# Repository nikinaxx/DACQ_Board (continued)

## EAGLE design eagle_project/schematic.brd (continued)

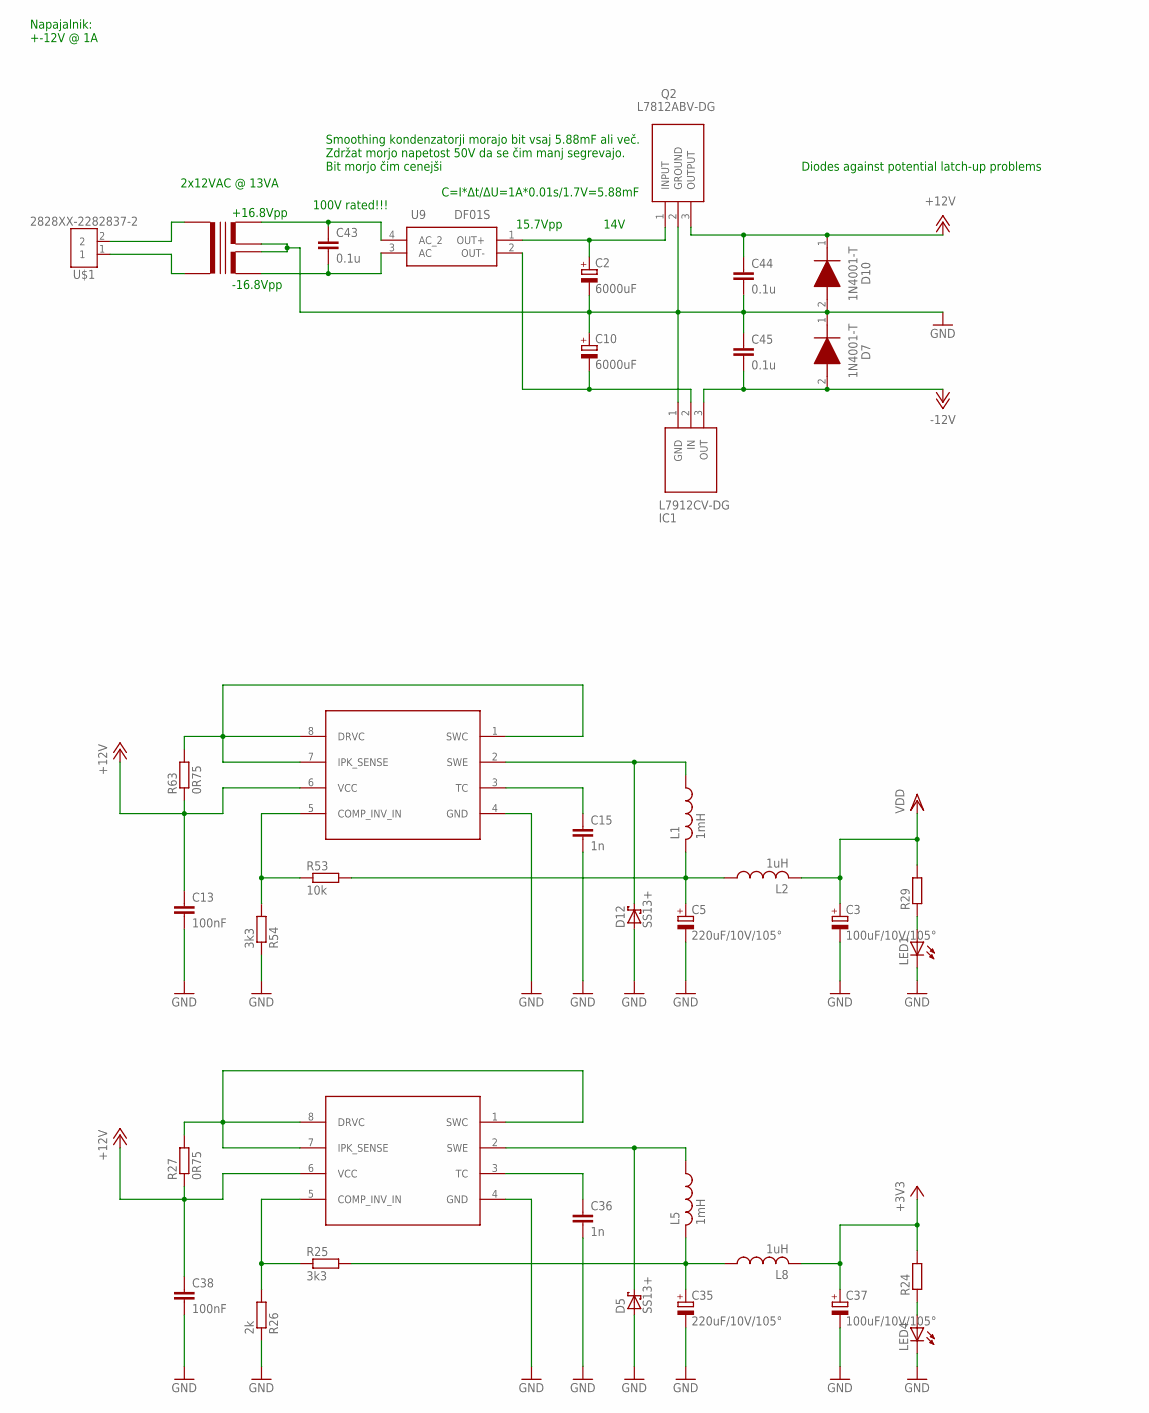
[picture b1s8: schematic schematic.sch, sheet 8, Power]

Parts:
C2, C10: 6000uF; EB22,5D
C3, C37: 100uF/10V/105°; E2-5
C5, C35: 220uF/10V/105°; E2,5-6
C13, C38: 100nF; C0805
C15, C36: 1n; C0805
C43, C44, C45: 0.1u; C0805
D5, D12: SS13+; SMC
D7, D10: 1N4001-T; DIOAD1408W86L464D236
IC1: L7912CV-DG; TO255P460X1020X2008-3P
IC3, IC7: AZ34063U; SO08
L1, L5: 1mH; 12LRS105C
L2, L8: 1uH; R0805
LED1, LED4: LED3MM
Q2: L7812ABV-DG; TO255P460X1020X2008-3P
R24, R29: R-EU_R0805; R0805
R25, R54: 3k3; R0805
R26: 2k; R0805
R27, R63: 0R75; R0805
R53: 10k; R0805
TR1: TRANSFORMER-PCB-2X12; TRANSFORMER-PCB-2X12_FOOTPRINT
U9: DF01S; SOT508P985X260-4N
U$1: 2828XX-2282837-2; TERMBLK_508-2N

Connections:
+3V3: C37.+, L8.2, R24.2; also elsewhere on the board
+5V: C5.+, L1.3 (2), L2.1, R53.2; also elsewhere on the board
+5V3: C35.+, L5.3 (2), L8.1, R25.2
+12V: C44.1, D10.1 (K), IC3.6 (VCC), IC7.6 (VCC), Q2.3 (OUTPUT), R27.1, R63.1; also elsewhere on the board
-12V: C45.2, D7.2 (A), IC1.3 (OUT); also elsewhere on the board
GND: C2.-, C3.-, C5.-, C10.+, C13.2, C15.2, C35.-, C36.2, C37.-, C38.2, C44.2, C45.1, D5.A, D7.1 (K), D10.2 (A), D12.A, IC1.1 (GND), IC3.4 (GND), IC7.4 (GND), LED1.K (C), LED4.K (C), Q2.2 (GROUND), R26.1, R54.1, TR1.S12, TR1.S21; also elsewhere on the board
unnamed: LED4.A, R24.1
unnamed: LED1.A, R29.1
unnamed: IC7.5 (COMP_INV_IN), R25.1, R26.2
unnamed: IC7.1 (SWC), IC7.7 (IPK_SENSE), IC7.8 (DRVC), R27.2
unnamed: D5.C, IC7.2 (SWE), L5.1
unnamed: C36.1, IC7.3 (TC)
unnamed: C15.1, IC3.3 (TC)
unnamed: IC3.5 (COMP_INV_IN), R53.1, R54.2
unnamed: IC3.1 (SWC), IC3.7 (IPK_SENSE), IC3.8 (DRVC), R63.2
unnamed: D12.C, IC3.2 (SWE), L1.1
unnamed: TR1.P2, U$1.1
unnamed: TR1.P1, U$1.2
unnamed: C43.1, TR1.S11, U9.4 (AC_2)
unnamed: C43.2, TR1.S22, U9.3 (AC)
unnamed: C2.+, Q2.1 (INPUT), U9.1 (OUT+)
unnamed: C10.-, IC1.2 (IN), U9.2 (OUT-)
VDD: C3.+, L2.2, R29.2; also elsewhere on the board
VDD1: C13.1
VDD2: C38.1

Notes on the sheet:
+16.8Vpp
-16.8Vpp
100V rated!!!
2x12VAC @ 13VA
15.7Vpp
Smoothing kondenzatorji morajo bit vsaj 5.88mF ali več. Zdržat morjo napetost 50V da se čim manj segrevajo. Bit morjo čim cenejši
C=I*Δt/ΔU=1A*0.01s/1.7V=5.88mF
14V
Diodes against potential latch-up problems
Napajalnik: +-12V @ 1A

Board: 2 copper layers, 210 parts (0 on the bottom side), 161 nets, no tracks yet.

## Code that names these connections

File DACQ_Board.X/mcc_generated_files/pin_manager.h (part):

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*/
/**
  @Summary
    Sets the GPIO pin, RA1, high using LATA1.

  @Description
    Sets the GPIO pin, RA1, high using LATA1.

  @Preconditions
    The RA1 must be set to an output.
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#define V_IN_0_10_1_SetHigh()          (_LATA1 = 1)
/**
  @Summary
    Sets the GPIO pin, RA1, low using LATA1.

  @Description
    Sets the GPIO pin, RA1, low using LATA1.

  @Preconditions
    The RA1 must be set to an output.
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#define V_IN_0_10_1_SetLow()           (_LATA1 = 0)
/**
  @Summary
    Toggles the GPIO pin, RA1, using LATA1.

  @Description
    Toggles the GPIO pin, RA1, using LATA1.

  @Preconditions
    The RA1 must be set to an output.
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#define V_IN_0_10_1_Toggle()           (_LATA1 ^= 1)
/**
  @Summary
    Reads the value of the GPIO pin, RA1.

  @Description
    Reads the value of the GPIO pin, RA1.

  @Preconditions
    None.
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    </code>

*/
#define V_IN_0_10_1_GetValue()         _RA1
/**
  @Summary
    Configures the GPIO pin, RA1, as an input.

  @Description
    Configures the GPIO pin, RA1, as an input.

  @Preconditions
    None.
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#define V_IN_0_10_1_SetDigitalInput()  (_TRISA1 = 1)
/**
  @Summary
    Configures the GPIO pin, RA1, as an output.

  @Description
    Configures the GPIO pin, RA1, as an output.

  @Preconditions
    None.
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#define V_IN_0_10_1_SetDigitalOutput() (_TRISA1 = 0)
/**
  @Summary
    Sets the GPIO pin, RA4, high using LATA4.

  @Description
    Sets the GPIO pin, RA4, high using LATA4.

  @Preconditions
    The RA4 must be set to an output.
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#define D_OUT_0_SetHigh()          (_LATA4 = 1)
/**
  @Summary
    Sets the GPIO pin, RA4, low using LATA4.

  @Description
    Sets the GPIO pin, RA4, low using LATA4.

  @Preconditions
    The RA4 must be set to an output.
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#define D_OUT_0_SetLow()           (_LATA4 = 0)
/**
  @Summary
    Toggles the GPIO pin, RA4, using LATA4.

  @Description
    Toggles the GPIO pin, RA4, using LATA4.

  @Preconditions
    The RA4 must be set to an output.
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#define D_OUT_0_Toggle()           (_LATA4 ^= 1)
/**
  @Summary
    Reads the value of the GPIO pin, RA4.

  @Description
    Reads the value of the GPIO pin, RA4.

  @Preconditions
    None.
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    </code>

*/
#define D_OUT_0_GetValue()         _RA4
/**
  @Summary
    Configures the GPIO pin, RA4, as an input.

  @Description
    Configures the GPIO pin, RA4, as an input.

  @Preconditions
    None.
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#define D_OUT_0_SetDigitalInput()  (_TRISA4 = 1)
/**
  @Summary
    Configures the GPIO pin, RA4, as an output.

  @Description
    Configures the GPIO pin, RA4, as an output.

  @Preconditions
    None.
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#define D_OUT_0_SetDigitalOutput() (_TRISA4 = 0)
/**
  @Summary
    Sets the GPIO pin, RB0, high using LATB0.

  @Description
    Sets the GPIO pin, RB0, high using LATB0.

  @Preconditions
    The RB0 must be set to an output.
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#define I_IN_1_SetHigh()          (_LATB0 = 1)
/**
  @Summary
    Sets the GPIO pin, RB0, low using LATB0.

  @Description
    Sets the GPIO pin, RB0, low using LATB0.

  @Preconditions
    The RB0 must be set to an output.
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#define I_IN_1_SetLow()           (_LATB0 = 0)
/**
  @Summary
    Toggles the GPIO pin, RB0, using LATB0.

  @Description
    Toggles the GPIO pin, RB0, using LATB0.

  @Preconditions
    The RB0 must be set to an output.
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#define I_IN_1_Toggle()           (_LATB0 ^= 1)
/**
  @Summary
    Reads the value of the GPIO pin, RB0.

  @Description
    Reads the value of the GPIO pin, RB0.

  @Preconditions
    None.
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    </code>

*/
#define I_IN_1_GetValue()         _RB0
/**
  @Summary
    Configures the GPIO pin, RB0, as an input.

  @Description
    Configures the GPIO pin, RB0, as an input.

  @Preconditions
    None.
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#define I_IN_1_SetDigitalInput()  (_TRISB0 = 1)
/**
  @Summary
    Configures the GPIO pin, RB0, as an output.

  @Description
    Configures the GPIO pin, RB0, as an output.

  @Preconditions
    None.
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#define I_IN_1_SetDigitalOutput() (_TRISB0 = 0)
/**
  @Summary
    Sets the GPIO pin, RB1, high using LATB1.

  @Description
    Sets the GPIO pin, RB1, high using LATB1.

  @Preconditions
    The RB1 must be set to an output.
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#define I_IN_2_SetHigh()          (_LATB1 = 1)
/**
  @Summary
    Sets the GPIO pin, RB1, low using LATB1.

  @Description
    Sets the GPIO pin, RB1, low using LATB1.

  @Preconditions
    The RB1 must be set to an output.
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#define I_IN_2_SetLow()           (_LATB1 = 0)
/**
  @Summary
    Toggles the GPIO pin, RB1, using LATB1.

  @Description
    Toggles the GPIO pin, RB1, using LATB1.

  @Preconditions
    The RB1 must be set to an output.
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#define I_IN_2_Toggle()           (_LATB1 ^= 1)
/**
  @Summary
    Reads the value of the GPIO pin, RB1.

  @Description
    Reads the value of the GPIO pin, RB1.

  @Preconditions
    None.
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    </code>

*/
#define I_IN_2_GetValue()         _RB1
/**
  @Summary
    Configures the GPIO pin, RB1, as an input.

  @Description
    Configures the GPIO pin, RB1, as an input.

  @Preconditions
    None.
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#define I_IN_2_SetDigitalInput()  (_TRISB1 = 1)
/**
  @Summary
    Configures the GPIO pin, RB1, as an output.

  @Description
    Configures the GPIO pin, RB1, as an output.

  @Preconditions
    None.
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#define V_IN_neg_10_2_SetDigitalOutput() (_TRISB13 = 0)
/**
  @Summary
    Sets the GPIO pin, RB14, high using LATB14.

  @Description
    Sets the GPIO pin, RB14, high using LATB14.

  @Preconditions
    The RB14 must be set to an output.
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#define V_IN_neg_10_1_SetHigh()          (_LATB14 = 1)
/**
  @Summary
    Sets the GPIO pin, RB14, low using LATB14.

  @Description
    Sets the GPIO pin, RB14, low using LATB14.

  @Preconditions
    The RB14 must be set to an output.
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#define V_IN_neg_10_1_SetLow()           (_LATB14 = 0)
/**
  @Summary
    Toggles the GPIO pin, RB14, using LATB14.

  @Description
    Toggles the GPIO pin, RB14, using LATB14.

  @Preconditions
    The RB14 must be set to an output.
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#define V_IN_neg_10_1_Toggle()           (_LATB14 ^= 1)
/**
  @Summary
    Reads the value of the GPIO pin, RB14.

  @Description
    Reads the value of the GPIO pin, RB14.

  @Preconditions
    None.
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    </code>

*/
#define V_IN_neg_10_1_GetValue()         _RB14
/**
  @Summary
    Configures the GPIO pin, RB14, as an input.

  @Description
    Configures the GPIO pin, RB14, as an input.

  @Preconditions
    None.
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#define V_IN_neg_10_1_SetDigitalInput()  (_TRISB14 = 1)
/**
  @Summary
    Configures the GPIO pin, RB14, as an output.

  @Description
    Configures the GPIO pin, RB14, as an output.

  @Preconditions
    None.
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#define V_IN_neg_10_1_SetDigitalOutput() (_TRISB14 = 0)
/**
  @Summary
    Sets the GPIO pin, RB15, high using LATB15.

  @Description
    Sets the GPIO pin, RB15, high using LATB15.

  @Preconditions
    The RB15 must be set to an output.
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#define V_IN_0_10_2_SetHigh()          (_LATB15 = 1)
/**
  @Summary
    Sets the GPIO pin, RB15, low using LATB15.

  @Description
    Sets the GPIO pin, RB15, low using LATB15.

  @Preconditions
    The RB15 must be set to an output.
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#define V_IN_0_10_2_SetLow()           (_LATB15 = 0)
/**
  @Summary
    Toggles the GPIO pin, RB15, using LATB15.

  @Description
    Toggles the GPIO pin, RB15, using LATB15.

  @Preconditions
    The RB15 must be set to an output.
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#define V_IN_0_10_2_Toggle()           (_LATB15 ^= 1)
/**
  @Summary
    Reads the value of the GPIO pin, RB15.

  @Description
    Reads the value of the GPIO pin, RB15.

  @Preconditions
    None.
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    </code>

*/
#define V_IN_0_10_2_GetValue()         _RB15
/**
  @Summary
    Configures the GPIO pin, RB15, as an input.

  @Description
    Configures the GPIO pin, RB15, as an input.

  @Preconditions
    None.
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#define V_IN_0_10_2_SetDigitalInput()  (_TRISB15 = 1)
/**
  @Summary
    Configures the GPIO pin, RB15, as an output.

  @Description
    Configures the GPIO pin, RB15, as an output.

  @Preconditions
    None.
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#define V_IN_0_10_2_SetDigitalOutput() (_TRISB15 = 0)
/**
  @Summary
    Sets the GPIO pin, RB2, high using LATB2.

  @Description
    Sets the GPIO pin, RB2, high using LATB2.

  @Preconditions
    The RB2 must be set to an output.
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#define D_IN_0_SetHigh()          (_LATB2 = 1)
/**
  @Summary
    Sets the GPIO pin, RB2, low using LATB2.

  @Description
    Sets the GPIO pin, RB2, low using LATB2.

  @Preconditions
    The RB2 must be set to an output.
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#define D_IN_0_SetLow()           (_LATB2 = 0)
/**
  @Summary
    Toggles the GPIO pin, RB2, using LATB2.

  @Description
    Toggles the GPIO pin, RB2, using LATB2.

  @Preconditions
    The RB2 must be set to an output.
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#define D_IN_0_Toggle()           (_LATB2 ^= 1)
/**
  @Summary
    Reads the value of the GPIO pin, RB2.

  @Description
    Reads the value of the GPIO pin, RB2.

  @Preconditions
    None.
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    </code>

*/
#define D_IN_0_GetValue()         _RB2
/**
  @Summary
    Configures the GPIO pin, RB2, as an input.

  @Description
    Configures the GPIO pin, RB2, as an input.

  @Preconditions
    None.
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#define D_IN_0_SetDigitalInput()  (_TRISB2 = 1)
/**
  @Summary
    Configures the GPIO pin, RB2, as an output.

  @Description
    Configures the GPIO pin, RB2, as an output.
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
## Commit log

2022-06-10 Added eagle project and DAC schematic.
2022-06-13 Zdruzene reference in dac v end sch
2022-06-26 koncane reference in napajanje
2022-07-08 Updated analog outputs. Removed op amps and added secector switches
2022-07-08 Analog outputs: added trimmers and fixed voltage labels
2022-08-13 schematic mostly done. added mp lab project
2022-08-15 changed R values in AO and changed DI
2022-08-17 Reverted DI. Added linear +-12V PSU with transformer
